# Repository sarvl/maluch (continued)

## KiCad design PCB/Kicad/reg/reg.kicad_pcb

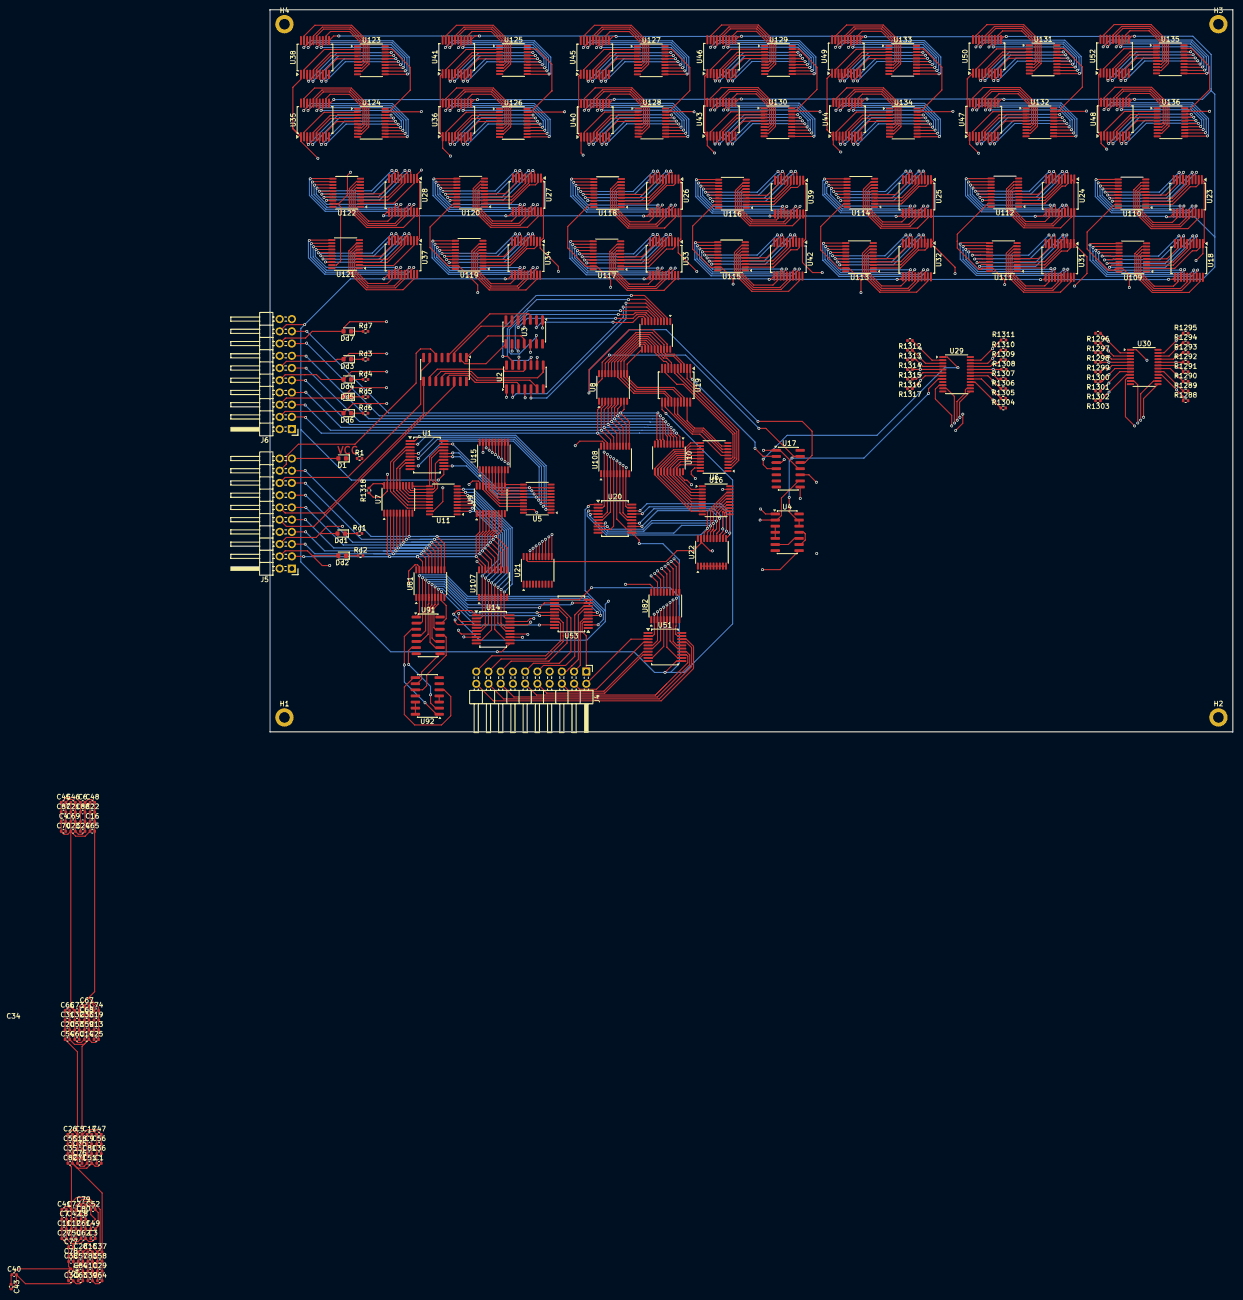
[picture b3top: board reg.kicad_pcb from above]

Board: 6 copper layers, 200.0 x 150.0 mm, 226 parts (0 on the bottom side), 428 nets.

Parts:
C1, C3, C4, C5, C6, C7, C8, C9, C10, C11, C12, C13, C14, C15, C16, C17, C18, C19, C20, C21, C22, C23, C24, C25, C26, C27, C28, C29, C30, C31, C32, C33, C34, C35, C36, C37, C38, C39, C40, C41, C42, C43, C44, C45, C46, C47, C48, C49, C50, C51, C52, C53, C54, C55, C56, C57, C58, C59, C60, C61, C62, C63, C64, C65, C66, C67, C68, C69, C70, C71, C72, C73, C74, C75, C76, C77, C78, C79, C80, C81, C82, C83, C84, C87, C88: 100nF; C_0402_1005Metric
D1: green; D_0603_1608Metric
Dd1, Dd2, Dd3, Dd4, Dd5, Dd6, Dd7: yellow; LED_0603_1608Metric
H1, H2, H3, H4: MountingHole_Pad; MountingHole_2.2mm_M2_DIN965_Pad
J4, J5, J6: Conn_02x10_Odd_Even; PinHeader_2x10_P2.54mm_Horizontal
R1: 680; R_0402_1005Metric
R1288, R1289, R1290, R1291, R1292, R1293, R1294, R1295, R1296, R1297, R1298, R1299, R1300, R1301, R1302, R1303, R1304, R1305, R1306, R1307, R1308, R1309, R1310, R1311, R1312, R1313, R1314, R1315, R1316, R1317, R1318: 10k; R_0402_1005Metric
Rd1, Rd2, Rd3, Rd4, Rd5, Rd6, Rd7: 680; R_0402_1005Metric
U1, U14, U18, U19, U20, U23, U24, U25, U26, U27, U28, U31, U32, U33, U34, U35, U36, U37, U38, U39, U40, U41, U42, U43, U44, U45, U46, U47, U48, U49, U50, U51, U52, U53: 74377; SSOP-20_5.3x7.2mm_P0.65mm
U2, U3, U4: 7400; SO-14_3.9x8.65mm_P1.27mm
U5, U6, U7, U8, U9, U10, U11, U12, U15, U16, U21, U22, U81, U82, U107, U108, U109, U110, U111, U112, U113, U114, U115, U116, U117, U118, U119, U120, U121, U122, U123, U124, U125, U126, U127, U128, U129, U130, U131, U132, U133, U134, U135, U136: 74245; TSSOP-20_4.4x6.5mm_P0.65mm
U17: 7404; SO-14_3.9x8.65mm_P1.27mm
U29, U30: 744067; TSSOP-24_4.4x7.8mm_P0.65mm
U85: 74148; SOIC-16_3.9x9.9mm_P1.27mm
U91, U92: 7408; SO-14_3.9x8.65mm_P1.27mm

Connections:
+5V: C1.1, C3.1, C4.1, C5.1, C6.1, C7.1, C8.1, C9.1, C10.1, C11.1, C12.1, C13.1, C14.1, C15.1, C16.1, C17.1, C18.1, C19.1, C20.1, C21.1, C22.1, C23.1, C24.1, C25.1, C26.1, C27.1, C28.1, C29.1, C30.1, C31.1, C32.1, C33.1, C34.1, C35.1, C36.1, C37.1, C38.1, C39.1, C40.1, C41.1, C42.1, C43.1, C44.1, C45.1, C46.1, C47.1, C48.1, C49.1, C50.1, C51.1, C52.1, C53.1, C54.1, C55.1, C56.1, C57.1, C58.1, C59.1, C60.1, C61.1, C62.1, C63.1, C64.1, C65.1, C66.1, C67.1, C68.1, C69.1, C70.1, C71.1, C72.1, C73.1, C74.1, C75.1, C76.1, C77.1, C78.1, C79.1, C80.1, C81.1, C82.1, C83.1, C84.1, C87.1, C88.1, D1.2 (A), J5.1, J5.19, J6.1, J6.19, R1288.2, R1289.2, R1290.2, R1291.2, R1292.2, R1293.2, R1294.2, R1295.2, R1296.2, R1297.2, R1298.2, R1299.2, R1300.2, R1301.2, R1302.2, R1303.2, R1304.2, R1305.2, R1306.2, R1307.2, R1308.2, R1309.2, R1310.2, R1311.2, R1312.2, R1313.2, R1314.2, R1315.2, R1316.2, R1317.2, R1318.2, U1.20 (VCC), U2.14 (VCC), U3.14 (VCC), U4.14 (VCC), U5.1 (A->B), U5.20 (VCC), U6.1 (A->B), U6.20 (VCC), U7.1 (A->B), U7.20 (VCC), U8.1 (A->B), U8.20 (VCC), U9.1 (A->B), U9.20 (VCC), U10.1 (A->B), U10.20 (VCC), U11.1 (A->B), U11.20 (VCC), U12.1 (A->B), U12.20 (VCC), U14.20 (VCC), U15.1 (A->B), U15.20 (VCC), U16.1 (A->B), U16.20 (VCC), U17.5, U17.14 (VCC), U18.20 (VCC), U19.20 (VCC), U20.20 (VCC), U21.1 (A->B), U21.20 (VCC), U22.1 (A->B), U22.20 (VCC), U23.20 (VCC), U24.20 (VCC), U25.20 (VCC), U26.20 (VCC), U27.20 (VCC), U28.20 (VCC), U29.15 (~E), U29.24 (VCC), U30.15 (~E), U30.24 (VCC), U31.20 (VCC), U32.20 (VCC), U33.20 (VCC), U34.20 (VCC), U35.20 (VCC), U36.20 (VCC), U37.20 (VCC), U38.20 (VCC), U39.20 (VCC), U40.20 (VCC), U41.20 (VCC), U42.20 (VCC), U43.20 (VCC), U44.20 (VCC), U45.20 (VCC), U46.20 (VCC), U47.20 (VCC), U48.20 (VCC), U49.20 (VCC), U50.20 (VCC), U51.20 (VCC), U52.20 (VCC), U53.20 (VCC), U81.1 (A->B), U81.20 (VCC), U82.1 (A->B), U82.20 (VCC), U85.16 (VCC), U91.14 (VCC), U92.12, U92.13, U92.14 (VCC), U107.1 (A->B), U107.20 (VCC), U108.1 (A->B), U108.20 (VCC), U109.1 (A->B), U109.20 (VCC), U110.1 (A->B), U110.20 (VCC), U111.1 (A->B), U111.20 (VCC), U112.1 (A->B), U112.20 (VCC), U113.1 (A->B), U113.20 (VCC), U114.1 (A->B), U114.20 (VCC), U115.1 (A->B), U115.20 (VCC), U116.1 (A->B), U116.20 (VCC), U117.1 (A->B), U117.20 (VCC), U118.1 (A->B), U118.20 (VCC), U119.1 (A->B), U119.20 (VCC), U120.1 (A->B), U120.20 (VCC), U121.1 (A->B), U121.20 (VCC), U122.1 (A->B), U122.20 (VCC), U123.1 (A->B), U123.20 (VCC), U124.1 (A->B), U124.20 (VCC), U125.1 (A->B), U125.20 (VCC), U126.1 (A->B), U126.20 (VCC), U127.1 (A->B), U127.20 (VCC), U128.1 (A->B), U128.20 (VCC), U129.1 (A->B), U129.20 (VCC), U130.1 (A->B), U130.20 (VCC), U131.1 (A->B), U131.20 (VCC), U132.1 (A->B), U132.20 (VCC), U133.1 (A->B), U133.20 (VCC), U134.1 (A->B), U134.20 (VCC), U135.1 (A->B), U135.20 (VCC), U136.1 (A->B), U136.20 (VCC)
/16 bit buffor3/n0E2: U5.19 (CE), U6.19 (CE), U17.8
/16 bit buffor21/OUT0: U5.18 (B0), U9.18 (B0), U15.2 (A0)
/16 bit buffor21/OUT1: U5.17 (B1), U9.17 (B1), U15.3 (A1)
/16 bit buffor21/OUT2: U5.16 (B2), U9.16 (B2), U15.4 (A2)
/16 bit buffor21/OUT3: U5.15 (B3), U9.15 (B3), U15.5 (A3)
/16 bit buffor21/OUT4: U5.14 (B4), U9.14 (B4), U15.6 (A4)
/16 bit buffor21/OUT5: U5.13 (B5), U9.13 (B5), U15.7 (A5)
/16 bit buffor21/OUT6: U5.12 (B6), U9.12 (B6), U15.8 (A6)
/16 bit buffor21/OUT7: U5.11 (B7), U9.11 (B7), U15.9 (A7)
/16 bit buffor21/OUT8: U6.18 (B0), U10.18 (B0), U16.2 (A0)
/16 bit buffor21/OUT9: U6.17 (B1), U10.17 (B1), U16.3 (A1)
/16 bit buffor21/OUT10: U6.16 (B2), U10.16 (B2), U16.4 (A2)
/16 bit buffor21/OUT11: U6.15 (B3), U10.15 (B3), U16.5 (A3)
/16 bit buffor21/OUT12: U6.14 (B4), U10.14 (B4), U16.6 (A4)
/16 bit buffor21/OUT13: U6.13 (B5), U10.13 (B5), U16.7 (A5)
/16 bit buffor21/OUT14: U6.12 (B6), U10.12 (B6), U16.8 (A6)
/16 bit buffor21/OUT15: U6.11 (B7), U10.11 (B7), U16.9 (A7)
/16 bit buffor23/OUT0: U1.3 (D0), U7.18 (B0), U11.18 (B0)
/16 bit buffor23/OUT1: U1.4 (D1), U7.17 (B1), U11.17 (B1)
/16 bit buffor23/OUT2: U1.7 (D2), U7.16 (B2), U11.16 (B2)
/16 bit buffor23/OUT3: U1.8 (D3), U7.15 (B3), U11.15 (B3)
/16 bit buffor23/OUT4: U1.13 (D4), U7.14 (B4), U11.14 (B4)
/16 bit buffor23/OUT5: U1.14 (D5), U7.13 (B5), U11.13 (B5)
/16 bit buffor23/OUT6: U1.17 (D6), U7.12 (B6), U11.12 (B6)
/16 bit buffor23/OUT7: U1.18 (D7), U7.11 (B7), U11.11 (B7)
/16 bit buffor23/OUT8: U8.18 (B0), U12.18 (B0), U19.3 (D0)
/16 bit buffor23/OUT9: U8.17 (B1), U12.17 (B1), U19.4 (D1)
/16 bit buffor23/OUT10: U8.16 (B2), U12.16 (B2), U19.7 (D2)
/16 bit buffor23/OUT11: U8.15 (B3), U12.15 (B3), U19.8 (D3)
/16 bit buffor23/OUT12: U8.14 (B4), U12.14 (B4), U19.13 (D4)
/16 bit buffor23/OUT13: U8.13 (B5), U12.13 (B5), U19.14 (D5)
/16 bit buffor23/OUT14: U8.12 (B6), U12.12 (B6), U19.17 (D6)
/16 bit buffor23/OUT15: U8.11 (B7), U12.11 (B7), U19.18 (D7)
/16 bit buffor23/n0E2: U11.19 (CE), U12.19 (CE), U17.12
/16 bit buffor25/OUT0: U14.3 (D0), U15.18 (B0), U21.18 (B0)
/16 bit buffor25/OUT1: U14.4 (D1), U15.17 (B1), U21.17 (B1)
/16 bit buffor25/OUT2: U14.7 (D2), U15.16 (B2), U21.16 (B2)
/16 bit buffor25/OUT3: U14.8 (D3), U15.15 (B3), U21.15 (B3)
/16 bit buffor25/OUT4: U14.13 (D4), U15.14 (B4), U21.14 (B4)
/16 bit buffor25/OUT5: U14.14 (D5), U15.13 (B5), U21.13 (B5)
/16 bit buffor25/OUT6: U14.17 (D6), U15.12 (B6), U21.12 (B6)
/16 bit buffor25/OUT7: U14.18 (D7), U15.11 (B7), U21.11 (B7)
/16 bit buffor25/OUT8: U16.18 (B0), U20.3 (D0), U22.18 (B0)
/16 bit buffor25/OUT9: U16.17 (B1), U20.4 (D1), U22.17 (B1)
/16 bit buffor25/OUT10: U16.16 (B2), U20.7 (D2), U22.16 (B2)
/16 bit buffor25/OUT11: U16.15 (B3), U20.8 (D3), U22.15 (B3)
/16 bit buffor25/OUT12: U16.14 (B4), U20.13 (D4), U22.14 (B4)
/16 bit buffor25/OUT13: U16.13 (B5), U20.14 (D5), U22.13 (B5)
/16 bit buffor25/OUT14: U16.12 (B6), U20.17 (D6), U22.12 (B6)
/16 bit buffor25/OUT15: U16.11 (B7), U20.18 (D7), U22.11 (B7)
/16 bit buffor26/n0E2: U17.10, U21.19 (CE), U22.19 (CE)
/16 bit buffor28/IN_1_0: U18.2 (Q0), U109.2 (A0)
/16 bit buffor28/IN_1_1: U18.5 (Q1), U109.3 (A1)
/16 bit buffor28/IN_1_2: U18.6 (Q2), U109.4 (A2)
/16 bit buffor28/IN_1_3: U18.9 (Q3), U109.5 (A3)
/16 bit buffor28/IN_1_4: U18.12 (Q4), U109.6 (A4)
/16 bit buffor28/IN_1_5: U18.15 (Q5), U109.7 (A5)
/16 bit buffor28/IN_1_6: U18.16 (Q6), U109.8 (A6)
/16 bit buffor28/IN_1_7: U18.19 (Q7), U109.9 (A7)
/16 bit buffor28/IN_1_8: U23.2 (Q0), U110.2 (A0)
/16 bit buffor28/IN_1_9: U23.5 (Q1), U110.3 (A1)
/16 bit buffor28/IN_1_10: U23.6 (Q2), U110.4 (A2)
/16 bit buffor28/IN_1_11: U23.9 (Q3), U110.5 (A3)
/16 bit buffor28/IN_1_12: U23.12 (Q4), U110.6 (A4)
/16 bit buffor28/IN_1_13: U23.15 (Q5), U110.7 (A5)
/16 bit buffor28/IN_1_14: U23.16 (Q6), U110.8 (A6)
/16 bit buffor28/IN_1_15: U23.19 (Q7), U110.9 (A7)
/16 bit buffor29/IN_1_0: U31.2 (Q0), U111.2 (A0)
/16 bit buffor29/IN_1_1: U31.5 (Q1), U111.3 (A1)
/16 bit buffor29/IN_1_2: U31.6 (Q2), U111.4 (A2)
/16 bit buffor29/IN_1_3: U31.9 (Q3), U111.5 (A3)
/16 bit buffor29/IN_1_4: U31.12 (Q4), U111.6 (A4)
/16 bit buffor29/IN_1_5: U31.15 (Q5), U111.7 (A5)
/16 bit buffor29/IN_1_6: U31.16 (Q6), U111.8 (A6)
/16 bit buffor29/IN_1_7: U31.19 (Q7), U111.9 (A7)
/16 bit buffor29/IN_1_8: U24.2 (Q0), U112.2 (A0)
/16 bit buffor29/IN_1_9: U24.5 (Q1), U112.3 (A1)
/16 bit buffor29/IN_1_10: U24.6 (Q2), U112.4 (A2)
/16 bit buffor29/IN_1_11: U24.9 (Q3), U112.5 (A3)
/16 bit buffor29/IN_1_12: U24.12 (Q4), U112.6 (A4)
/16 bit buffor29/IN_1_13: U24.15 (Q5), U112.7 (A5)
/16 bit buffor29/IN_1_14: U24.16 (Q6), U112.8 (A6)
/16 bit buffor29/IN_1_15: U24.19 (Q7), U112.9 (A7)
/16 bit buffor30/IN_1_0: U32.2 (Q0), U113.2 (A0)
/16 bit buffor30/IN_1_1: U32.5 (Q1), U113.3 (A1)
/16 bit buffor30/IN_1_2: U32.6 (Q2), U113.4 (A2)
/16 bit buffor30/IN_1_3: U32.9 (Q3), U113.5 (A3)
/16 bit buffor30/IN_1_4: U32.12 (Q4), U113.6 (A4)
/16 bit buffor30/IN_1_5: U32.15 (Q5), U113.7 (A5)
/16 bit buffor30/IN_1_6: U32.16 (Q6), U113.8 (A6)
/16 bit buffor30/IN_1_7: U32.19 (Q7), U113.9 (A7)
/16 bit buffor30/IN_1_8: U25.2 (Q0), U114.2 (A0)
/16 bit buffor30/IN_1_9: U25.5 (Q1), U114.3 (A1)
/16 bit buffor30/IN_1_10: U25.6 (Q2), U114.4 (A2)
/16 bit buffor30/IN_1_11: U25.9 (Q3), U114.5 (A3)
/16 bit buffor30/IN_1_12: U25.12 (Q4), U114.6 (A4)
/16 bit buffor30/IN_1_13: U25.15 (Q5), U114.7 (A5)
/16 bit buffor30/IN_1_14: U25.16 (Q6), U114.8 (A6)
/16 bit buffor30/IN_1_15: U25.19 (Q7), U114.9 (A7)
/16 bit buffor31/IN_1_0: U42.2 (Q0), U115.2 (A0)
/16 bit buffor31/IN_1_1: U42.5 (Q1), U115.3 (A1)
/16 bit buffor31/IN_1_2: U42.6 (Q2), U115.4 (A2)
/16 bit buffor31/IN_1_3: U42.9 (Q3), U115.5 (A3)
/16 bit buffor31/IN_1_4: U42.12 (Q4), U115.6 (A4)
/16 bit buffor31/IN_1_5: U42.15 (Q5), U115.7 (A5)
/16 bit buffor31/IN_1_6: U42.16 (Q6), U115.8 (A6)
/16 bit buffor31/IN_1_7: U42.19 (Q7), U115.9 (A7)
/16 bit buffor31/IN_1_8: U39.2 (Q0), U116.2 (A0)
/16 bit buffor31/IN_1_9: U39.5 (Q1), U116.3 (A1)
/16 bit buffor31/IN_1_10: U39.6 (Q2), U116.4 (A2)
/16 bit buffor31/IN_1_11: U39.9 (Q3), U116.5 (A3)
/16 bit buffor31/IN_1_12: U39.12 (Q4), U116.6 (A4)
/16 bit buffor31/IN_1_13: U39.15 (Q5), U116.7 (A5)
/16 bit buffor31/IN_1_14: U39.16 (Q6), U116.8 (A6)
/16 bit buffor31/IN_1_15: U39.19 (Q7), U116.9 (A7)
/16 bit buffor32/IN_1_0: U33.2 (Q0), U117.2 (A0)
/16 bit buffor32/IN_1_1: U33.5 (Q1), U117.3 (A1)
/16 bit buffor32/IN_1_2: U33.6 (Q2), U117.4 (A2)
/16 bit buffor32/IN_1_3: U33.9 (Q3), U117.5 (A3)
/16 bit buffor32/IN_1_4: U33.12 (Q4), U117.6 (A4)
/16 bit buffor32/IN_1_5: U33.15 (Q5), U117.7 (A5)
/16 bit buffor32/IN_1_6: U33.16 (Q6), U117.8 (A6)
/16 bit buffor32/IN_1_7: U33.19 (Q7), U117.9 (A7)
/16 bit buffor32/IN_1_8: U26.2 (Q0), U118.2 (A0)
/16 bit buffor32/IN_1_9: U26.5 (Q1), U118.3 (A1)
/16 bit buffor32/IN_1_10: U26.6 (Q2), U118.4 (A2)
/16 bit buffor32/IN_1_11: U26.9 (Q3), U118.5 (A3)
/16 bit buffor32/IN_1_12: U26.12 (Q4), U118.6 (A4)
/16 bit buffor32/IN_1_13: U26.15 (Q5), U118.7 (A5)
/16 bit buffor32/IN_1_14: U26.16 (Q6), U118.8 (A6)
/16 bit buffor32/IN_1_15: U26.19 (Q7), U118.9 (A7)
/16 bit buffor33/IN_1_0: U34.2 (Q0), U119.2 (A0)
/16 bit buffor33/IN_1_1: U34.5 (Q1), U119.3 (A1)
/16 bit buffor33/IN_1_2: U34.6 (Q2), U119.4 (A2)
/16 bit buffor33/IN_1_3: U34.9 (Q3), U119.5 (A3)
/16 bit buffor33/IN_1_4: U34.12 (Q4), U119.6 (A4)
/16 bit buffor33/IN_1_5: U34.15 (Q5), U119.7 (A5)
/16 bit buffor33/IN_1_6: U34.16 (Q6), U119.8 (A6)
/16 bit buffor33/IN_1_7: U34.19 (Q7), U119.9 (A7)
/16 bit buffor33/IN_1_8: U27.2 (Q0), U120.2 (A0)
/16 bit buffor33/IN_1_9: U27.5 (Q1), U120.3 (A1)
/16 bit buffor33/IN_1_10: U27.6 (Q2), U120.4 (A2)
/16 bit buffor33/IN_1_11: U27.9 (Q3), U120.5 (A3)
/16 bit buffor33/IN_1_12: U27.12 (Q4), U120.6 (A4)
/16 bit buffor33/IN_1_13: U27.15 (Q5), U120.7 (A5)
/16 bit buffor33/IN_1_14: U27.16 (Q6), U120.8 (A6)
/16 bit buffor33/IN_1_15: U27.19 (Q7), U120.9 (A7)
/16 bit buffor34/IN_1_0: U37.2 (Q0), U121.2 (A0)
/16 bit buffor34/IN_1_1: U37.5 (Q1), U121.3 (A1)
/16 bit buffor34/IN_1_2: U37.6 (Q2), U121.4 (A2)
/16 bit buffor34/IN_1_3: U37.9 (Q3), U121.5 (A3)
/16 bit buffor34/IN_1_4: U37.12 (Q4), U121.6 (A4)
/16 bit buffor34/IN_1_5: U37.15 (Q5), U121.7 (A5)
/16 bit buffor34/IN_1_6: U37.16 (Q6), U121.8 (A6)
/16 bit buffor34/IN_1_7: U37.19 (Q7), U121.9 (A7)
/16 bit buffor34/IN_1_8: U28.2 (Q0), U122.2 (A0)
/16 bit buffor34/IN_1_9: U28.5 (Q1), U122.3 (A1)
/16 bit buffor34/IN_1_10: U28.6 (Q2), U122.4 (A2)
/16 bit buffor34/IN_1_11: U28.9 (Q3), U122.5 (A3)
/16 bit buffor34/IN_1_12: U28.12 (Q4), U122.6 (A4)
/16 bit buffor34/IN_1_13: U28.15 (Q5), U122.7 (A5)
/16 bit buffor34/IN_1_14: U28.16 (Q6), U122.8 (A6)
/16 bit buffor34/IN_1_15: U28.19 (Q7), U122.9 (A7)
/16 bit buffor35/IN_1_0: U38.2 (Q0), U123.2 (A0)
/16 bit buffor35/IN_1_1: U38.5 (Q1), U123.3 (A1)
/16 bit buffor35/IN_1_2: U38.6 (Q2), U123.4 (A2)
/16 bit buffor35/IN_1_3: U38.9 (Q3), U123.5 (A3)
/16 bit buffor35/IN_1_4: U38.12 (Q4), U123.6 (A4)
/16 bit buffor35/IN_1_5: U38.15 (Q5), U123.7 (A5)
/16 bit buffor35/IN_1_6: U38.16 (Q6), U123.8 (A6)
/16 bit buffor35/IN_1_7: U38.19 (Q7), U123.9 (A7)
/16 bit buffor35/IN_1_8: U35.2 (Q0), U124.2 (A0)
/16 bit buffor35/IN_1_9: U35.5 (Q1), U124.3 (A1)
/16 bit buffor35/IN_1_10: U35.6 (Q2), U124.4 (A2)
/16 bit buffor35/IN_1_11: U35.9 (Q3), U124.5 (A3)
/16 bit buffor35/IN_1_12: U35.12 (Q4), U124.6 (A4)
/16 bit buffor35/IN_1_13: U35.15 (Q5), U124.7 (A5)
/16 bit buffor35/IN_1_14: U35.16 (Q6), U124.8 (A6)
/16 bit buffor35/IN_1_15: U35.19 (Q7), U124.9 (A7)
/16 bit buffor36/IN_1_0: U41.2 (Q0), U125.2 (A0)
/16 bit buffor36/IN_1_1: U41.5 (Q1), U125.3 (A1)
/16 bit buffor36/IN_1_2: U41.6 (Q2), U125.4 (A2)
/16 bit buffor36/IN_1_3: U41.9 (Q3), U125.5 (A3)
/16 bit buffor36/IN_1_4: U41.12 (Q4), U125.6 (A4)
/16 bit buffor36/IN_1_5: U41.15 (Q5), U125.7 (A5)
/16 bit buffor36/IN_1_6: U41.16 (Q6), U125.8 (A6)
/16 bit buffor36/IN_1_7: U41.19 (Q7), U125.9 (A7)
/16 bit buffor36/IN_1_8: U36.2 (Q0), U126.2 (A0)
/16 bit buffor36/IN_1_9: U36.5 (Q1), U126.3 (A1)
/16 bit buffor36/IN_1_10: U36.6 (Q2), U126.4 (A2)
/16 bit buffor36/IN_1_11: U36.9 (Q3), U126.5 (A3)
/16 bit buffor36/IN_1_12: U36.12 (Q4), U126.6 (A4)
/16 bit buffor36/IN_1_13: U36.15 (Q5), U126.7 (A5)
/16 bit buffor36/IN_1_14: U36.16 (Q6), U126.8 (A6)
/16 bit buffor36/IN_1_15: U36.19 (Q7), U126.9 (A7)
/16 bit buffor37/IN_1_0: U45.2 (Q0), U127.2 (A0)
/16 bit buffor37/IN_1_1: U45.5 (Q1), U127.3 (A1)
/16 bit buffor37/IN_1_2: U45.6 (Q2), U127.4 (A2)
/16 bit buffor37/IN_1_3: U45.9 (Q3), U127.5 (A3)
/16 bit buffor37/IN_1_4: U45.12 (Q4), U127.6 (A4)
/16 bit buffor37/IN_1_5: U45.15 (Q5), U127.7 (A5)
/16 bit buffor37/IN_1_6: U45.16 (Q6), U127.8 (A6)
/16 bit buffor37/IN_1_7: U45.19 (Q7), U127.9 (A7)
/16 bit buffor37/IN_1_8: U40.2 (Q0), U128.2 (A0)
/16 bit buffor37/IN_1_9: U40.5 (Q1), U128.3 (A1)
/16 bit buffor37/IN_1_10: U40.6 (Q2), U128.4 (A2)
/16 bit buffor37/IN_1_11: U40.9 (Q3), U128.5 (A3)
/16 bit buffor37/IN_1_12: U40.12 (Q4), U128.6 (A4)
/16 bit buffor37/IN_1_13: U40.15 (Q5), U128.7 (A5)
/16 bit buffor37/IN_1_14: U40.16 (Q6), U128.8 (A6)
/16 bit buffor37/IN_1_15: U40.19 (Q7), U128.9 (A7)
/16 bit buffor38/IN_1_0: U46.2 (Q0), U129.2 (A0)
/16 bit buffor38/IN_1_1: U46.5 (Q1), U129.3 (A1)
/16 bit buffor38/IN_1_2: U46.6 (Q2), U129.4 (A2)
/16 bit buffor38/IN_1_3: U46.9 (Q3), U129.5 (A3)
/16 bit buffor38/IN_1_4: U46.12 (Q4), U129.6 (A4)
/16 bit buffor38/IN_1_5: U46.15 (Q5), U129.7 (A5)
/16 bit buffor38/IN_1_6: U46.16 (Q6), U129.8 (A6)
/16 bit buffor38/IN_1_7: U46.19 (Q7), U129.9 (A7)
/16 bit buffor38/IN_1_8: U43.2 (Q0), U130.2 (A0)
/16 bit buffor38/IN_1_9: U43.5 (Q1), U130.3 (A1)
/16 bit buffor38/IN_1_10: U43.6 (Q2), U130.4 (A2)
/16 bit buffor38/IN_1_11: U43.9 (Q3), U130.5 (A3)
/16 bit buffor38/IN_1_12: U43.12 (Q4), U130.6 (A4)
/16 bit buffor38/IN_1_13: U43.15 (Q5), U130.7 (A5)
/16 bit buffor38/IN_1_14: U43.16 (Q6), U130.8 (A6)
/16 bit buffor38/IN_1_15: U43.19 (Q7), U130.9 (A7)
/16 bit buffor39/IN_1_0: U50.2 (Q0), U131.2 (A0)
/16 bit buffor39/IN_1_1: U50.5 (Q1), U131.3 (A1)
/16 bit buffor39/IN_1_2: U50.6 (Q2), U131.4 (A2)
/16 bit buffor39/IN_1_3: U50.9 (Q3), U131.5 (A3)
/16 bit buffor39/IN_1_4: U50.12 (Q4), U131.6 (A4)
/16 bit buffor39/IN_1_5: U50.15 (Q5), U131.7 (A5)
/16 bit buffor39/IN_1_6: U50.16 (Q6), U131.8 (A6)
/16 bit buffor39/IN_1_7: U50.19 (Q7), U131.9 (A7)
/16 bit buffor39/IN_1_8: U47.2 (Q0), U132.2 (A0)
/16 bit buffor39/IN_1_9: U47.5 (Q1), U132.3 (A1)
/16 bit buffor39/IN_1_10: U47.6 (Q2), U132.4 (A2)
/16 bit buffor39/IN_1_11: U47.9 (Q3), U132.5 (A3)
/16 bit buffor39/IN_1_12: U47.12 (Q4), U132.6 (A4)
/16 bit buffor39/IN_1_13: U47.15 (Q5), U132.7 (A5)
/16 bit buffor39/IN_1_14: U47.16 (Q6), U132.8 (A6)
/16 bit buffor39/IN_1_15: U47.19 (Q7), U132.9 (A7)
/16 bit buffor40/IN_1_0: U49.2 (Q0), U133.2 (A0)
/16 bit buffor40/IN_1_1: U49.5 (Q1), U133.3 (A1)
/16 bit buffor40/IN_1_2: U49.6 (Q2), U133.4 (A2)
/16 bit buffor40/IN_1_3: U49.9 (Q3), U133.5 (A3)
/16 bit buffor40/IN_1_4: U49.12 (Q4), U133.6 (A4)
/16 bit buffor40/IN_1_5: U49.15 (Q5), U133.7 (A5)
/16 bit buffor40/IN_1_6: U49.16 (Q6), U133.8 (A6)
/16 bit buffor40/IN_1_7: U49.19 (Q7), U133.9 (A7)
/16 bit buffor40/IN_1_8: U44.2 (Q0), U134.2 (A0)
/16 bit buffor40/IN_1_9: U44.5 (Q1), U134.3 (A1)
/16 bit buffor40/IN_1_10: U44.6 (Q2), U134.4 (A2)
/16 bit buffor40/IN_1_11: U44.9 (Q3), U134.5 (A3)
/16 bit buffor40/IN_1_12: U44.12 (Q4), U134.6 (A4)
/16 bit buffor40/IN_1_13: U44.15 (Q5), U134.7 (A5)
/16 bit buffor40/IN_1_14: U44.16 (Q6), U134.8 (A6)
/16 bit buffor40/IN_1_15: U44.19 (Q7), U134.9 (A7)
/16 bit buffor41/IN_1_0: U52.2 (Q0), U135.2 (A0)
/16 bit buffor41/IN_1_1: U52.5 (Q1), U135.3 (A1)
/16 bit buffor41/IN_1_2: U52.6 (Q2), U135.4 (A2)
/16 bit buffor41/IN_1_3: U52.9 (Q3), U135.5 (A3)
/16 bit buffor41/IN_1_4: U52.12 (Q4), U135.6 (A4)
/16 bit buffor41/IN_1_5: U52.15 (Q5), U135.7 (A5)
/16 bit buffor41/IN_1_6: U52.16 (Q6), U135.8 (A6)
/16 bit buffor41/IN_1_7: U52.19 (Q7), U135.9 (A7)
/16 bit buffor41/IN_1_8: U48.2 (Q0), U136.2 (A0)
/16 bit buffor41/IN_1_9: U48.5 (Q1), U136.3 (A1)
/16 bit buffor41/IN_1_10: U48.6 (Q2), U136.4 (A2)
/16 bit buffor41/IN_1_11: U48.9 (Q3), U136.5 (A3)
/16 bit buffor41/IN_1_12: U48.12 (Q4), U136.6 (A4)
/16 bit buffor41/IN_1_13: U48.15 (Q5), U136.7 (A5)
/16 bit buffor41/IN_1_14: U48.16 (Q6), U136.8 (A6)
/16 bit buffor41/IN_1_15: U48.19 (Q7), U136.9 (A7)
/16 bit register17/nWE: U4.8, U14.1 (~E), U20.1 (~E)
/16 bit register18/nWE: U1.1 (~E), U17.2, U19.1 (~E)
/ID_REG_SEL_0: Dd6.2 (A), J6.4, U29.10 (S0), U30.10 (S0)
/ID_REG_SEL_1: Dd5.2 (A), J6.6, U29.11 (S1), U30.11 (S1)
/ID_REG_SEL_2: Dd4.2 (A), J6.10, U29.14 (S2), U30.14 (S2)
/ID_REG_SEL_3: Dd3.2 (A), J6.12, U29.13 (S3), U30.13 (S3)
/INT: J5.10, U85.14 (~GS)
/IO0: J4.1, U53.3 (D0)
/IO1: J4.3, U53.4 (D1)
/IO2: J4.5, U53.7 (D2)
/IO3: J4.9, U53.8 (D3)
/IO4: J4.11, U53.13 (D4)
/IO5: J4.15, U53.14 (D5)
/IO6: J4.17, U53.17 (D6)
/IO7: J4.19, U53.18 (D7)
/IO8: J4.2, U51.3 (D0)
/IO9: J4.4, U51.4 (D1)
/IO10: J4.6, U51.7 (D2)
/IO11: J4.10, U51.8 (D3)
/IO12: J4.12, U51.13 (D4)
/IO13: J4.16, U51.14 (D5)
/IO14: J4.18, U51.17 (D6)
/IO15: J4.20, U51.18 (D7)
/Interupt_ID_0: J5.12, U85.9 (~S0)
/Interupt_ID_1: J5.16, U85.7 (~S1)
/Interupt_ID_2: J5.18, U85.6 (~S2)
/OUT_1_2: R1317.1, U18.1 (~E), U23.1 (~E), U29.7 (I2)
/OUT_1_3: R1316.1, U24.1 (~E), U29.6 (I3), U31.1 (~E)
/OUT_1_4: R1315.1, U25.1 (~E), U29.5 (I4), U32.1 (~E)
/OUT_1_5: R1314.1, U29.4 (I5), U39.1 (~E), U42.1 (~E)
/OUT_1_6: R1313.1, U26.1 (~E), U29.3 (I6), U33.1 (~E)
/OUT_1_7: R1312.1, U27.1 (~E), U29.2 (I7), U34.1 (~E)
/OUT_1_8: R1311.1, U28.1 (~E), U29.23 (I8), U37.1 (~E)
/OUT_1_9: R1310.1, U29.22 (I9), U35.1 (~E), U38.1 (~E)
/OUT_1_10: R1309.1, U29.21 (I10), U36.1 (~E), U41.1 (~E)
/OUT_1_11: R1308.1, U29.20 (I11), U40.1 (~E), U45.1 (~E)
/OUT_1_12: R1307.1, U29.19 (I12), U43.1 (~E), U46.1 (~E)
/OUT_1_13: R1306.1, U29.18 (I13), U44.1 (~E), U49.1 (~E)
/OUT_1_14: R1305.1, U29.17 (I14), U47.1 (~E), U50.1 (~E)
/OUT_1_15: R1304.1, U29.16 (I15), U48.1 (~E), U52.1 (~E)
/OUT_5_0: U53.2 (Q0), U81.2 (A0), U91.1
/OUT_5_1: U53.5 (Q1), U81.3 (A1), U91.2
/OUT_5_2: U53.6 (Q2), U81.4 (A2), U91.4
/OUT_5_3: U53.9 (Q3), U81.5 (A3), U91.5
/OUT_5_4: U53.12 (Q4), U81.6 (A4), U91.9
/OUT_5_5: U53.15 (Q5), U81.7 (A5), U91.10
/OUT_5_6: U53.16 (Q6), U81.8 (A6), U91.12
/OUT_5_7: U53.19 (Q7), U81.9 (A7), U91.13
/OUT_5_8: U2.12, U51.2 (Q0), U82.2 (A0)
/OUT_5_9: U2.9, U51.5 (Q1), U82.3 (A1)
/OUT_5_10: U2.4, U51.6 (Q2), U82.4 (A2)
/OUT_5_11: U2.1, U51.9 (Q3), U82.5 (A3)
/OUT_5_12: U3.12, U51.12 (Q4), U82.6 (A4)
/OUT_5_13: U3.9, U51.15 (Q5), U82.7 (A5)
/OUT_5_14: U3.4, U51.16 (Q6), U82.8 (A6)
/OUT_5_15: U3.1, U51.19 (Q7), U82.9 (A7)
/OUT_7_0: R1303.1, U30.9 (I0), U81.19 (CE), U82.19 (CE)
/OUT_7_1: R1302.1, U30.8 (I1), U107.19 (CE), U108.19 (CE)
/OUT_7_2: R1301.1, U30.7 (I2), U109.19 (CE), U110.19 (CE)
/OUT_7_3: R1300.1, U30.6 (I3), U111.19 (CE), U112.19 (CE)
/OUT_7_4: R1299.1, U30.5 (I4), U113.19 (CE), U114.19 (CE)
/OUT_7_5: R1298.1, U30.4 (I5), U115.19 (CE), U116.19 (CE)
/OUT_7_6: R1297.1, U30.3 (I6), U117.19 (CE), U118.19 (CE)
/OUT_7_7: R1296.1, U30.2 (I7), U119.19 (CE), U120.19 (CE)
/OUT_7_8: R1295.1, U30.23 (I8), U121.19 (CE), U122.19 (CE)
/OUT_7_9: R1294.1, U30.22 (I9), U123.19 (CE), U124.19 (CE)
/OUT_7_10: R1293.1, U30.21 (I10), U125.19 (CE), U126.19 (CE)
/OUT_7_11: R1292.1, U30.20 (I11), U127.19 (CE), U128.19 (CE)
/OUT_7_12: R1291.1, U30.19 (I12), U129.19 (CE), U130.19 (CE)
/OUT_7_13: R1290.1, U30.18 (I13), U133.19 (CE), U134.19 (CE)
/OUT_7_14: R1289.1, U30.17 (I14), U131.19 (CE), U132.19 (CE)
/OUT_7_15: R1288.1, U30.16 (I15), U135.19 (CE), U136.19 (CE)
/clk: J6.18, U1.11 (CP), U14.11 (CP), U18.11 (CP), U19.11 (CP), U20.11 (CP), U23.11 (CP), U24.11 (CP), U25.11 (CP), U26.11 (CP), U27.11 (CP), U28.11 (CP), U31.11 (CP), U32.11 (CP), U33.11 (CP), U34.11 (CP), U35.11 (CP), U36.11 (CP), U37.11 (CP), U38.11 (CP), U39.11 (CP), U40.11 (CP), U41.11 (CP), U42.11 (CP), U43.11 (CP), U44.11 (CP), U45.11 (CP), U46.11 (CP), U47.11 (CP), U48.11 (CP), U49.11 (CP), U50.11 (CP), U51.11 (CP), U52.11 (CP), U53.11 (CP)
/data0: J5.3, U7.2 (A0), U9.2 (A0), U18.3 (D0), U31.3 (D0), U32.3 (D0), U33.3 (D0), U34.3 (D0), U37.3 (D0), U38.3 (D0), U41.3 (D0), U42.3 (D0), U45.3 (D0), U46.3 (D0), U49.3 (D0), U50.3 (D0), U52.3 (D0), U81.18 (B0), U107.18 (B0), U109.18 (B0), U111.18 (B0), U113.18 (B0), U115.18 (B0), U117.18 (B0), U119.18 (B0), U121.18 (B0), U123.18 (B0), U125.18 (B0), U127.18 (B0), U129.18 (B0), U131.18 (B0), U133.18 (B0), U135.18 (B0)
/data1: J5.5, U7.3 (A1), U9.3 (A1), U18.4 (D1), U31.4 (D1), U32.4 (D1), U33.4 (D1), U34.4 (D1), U37.4 (D1), U38.4 (D1), U41.4 (D1), U42.4 (D1), U45.4 (D1), U46.4 (D1), U49.4 (D1), U50.4 (D1), U52.4 (D1), U81.17 (B1), U107.17 (B1), U109.17 (B1), U111.17 (B1), U113.17 (B1), U115.17 (B1), U117.17 (B1), U119.17 (B1), U121.17 (B1), U123.17 (B1), U125.17 (B1), U127.17 (B1), U129.17 (B1), U131.17 (B1), U133.17 (B1), U135.17 (B1)
/data2: J5.7, U7.4 (A2), U9.4 (A2), U18.7 (D2), U31.7 (D2), U32.7 (D2), U33.7 (D2), U34.7 (D2), U37.7 (D2), U38.7 (D2), U41.7 (D2), U42.7 (D2), U45.7 (D2), U46.7 (D2), U49.7 (D2), U50.7 (D2), U52.7 (D2), U81.16 (B2), U107.16 (B2), U109.16 (B2), U111.16 (B2), U113.16 (B2), U115.16 (B2), U117.16 (B2), U119.16 (B2), U121.16 (B2), U123.16 (B2), U125.16 (B2), U127.16 (B2), U129.16 (B2), U131.16 (B2), U133.16 (B2), U135.16 (B2)
/data3: J5.9, U7.5 (A3), U9.5 (A3), U18.8 (D3), U31.8 (D3), U32.8 (D3), U33.8 (D3), U34.8 (D3), U37.8 (D3), U38.8 (D3), U41.8 (D3), U42.8 (D3), U45.8 (D3), U46.8 (D3), U49.8 (D3), U50.8 (D3), U52.8 (D3), U81.15 (B3), U107.15 (B3), U109.15 (B3), U111.15 (B3), U113.15 (B3), U115.15 (B3), U117.15 (B3), U119.15 (B3), U121.15 (B3), U123.15 (B3), U125.15 (B3), U127.15 (B3), U129.15 (B3), U131.15 (B3), U133.15 (B3), U135.15 (B3)
/data4: J5.11, U7.6 (A4), U9.6 (A4), U18.13 (D4), U31.13 (D4), U32.13 (D4), U33.13 (D4), U34.13 (D4), U37.13 (D4), U38.13 (D4), U41.13 (D4), U42.13 (D4), U45.13 (D4), U46.13 (D4), U49.13 (D4), U50.13 (D4), U52.13 (D4), U81.14 (B4), U107.14 (B4), U109.14 (B4), U111.14 (B4), U113.14 (B4), U115.14 (B4), U117.14 (B4), U119.14 (B4), U121.14 (B4), U123.14 (B4), U125.14 (B4), U127.14 (B4), U129.14 (B4), U131.14 (B4), U133.14 (B4), U135.14 (B4)
/data5: J5.13, U7.7 (A5), U9.7 (A5), U18.14 (D5), U31.14 (D5), U32.14 (D5), U33.14 (D5), U34.14 (D5), U37.14 (D5), U38.14 (D5), U41.14 (D5), U42.14 (D5), U45.14 (D5), U46.14 (D5), U49.14 (D5), U50.14 (D5), U52.14 (D5), U81.13 (B5), U107.13 (B5), U109.13 (B5), U111.13 (B5), U113.13 (B5), U115.13 (B5), U117.13 (B5), U119.13 (B5), U121.13 (B5), U123.13 (B5), U125.13 (B5), U127.13 (B5), U129.13 (B5), U131.13 (B5), U133.13 (B5), U135.13 (B5)
/data6: J5.15, U7.8 (A6), U9.8 (A6), U18.17 (D6), U31.17 (D6), U32.17 (D6), U33.17 (D6), U34.17 (D6), U37.17 (D6), U38.17 (D6), U41.17 (D6), U42.17 (D6), U45.17 (D6), U46.17 (D6), U49.17 (D6), U50.17 (D6), U52.17 (D6), U81.12 (B6), U107.12 (B6), U109.12 (B6), U111.12 (B6), U113.12 (B6), U115.12 (B6), U117.12 (B6), U119.12 (B6), U121.12 (B6), U123.12 (B6), U125.12 (B6), U127.12 (B6), U129.12 (B6), U131.12 (B6), U133.12 (B6), U135.12 (B6)
/data7: J5.17, U7.9 (A7), U9.9 (A7), U18.18 (D7), U31.18 (D7), U32.18 (D7), U33.18 (D7), U34.18 (D7), U37.18 (D7), U38.18 (D7), U41.18 (D7), U42.18 (D7), U45.18 (D7), U46.18 (D7), U49.18 (D7), U50.18 (D7), U52.18 (D7), U81.11 (B7), U107.11 (B7), U109.11 (B7), U111.11 (B7), U113.11 (B7), U115.11 (B7), U117.11 (B7), U119.11 (B7), U121.11 (B7), U123.11 (B7), U125.11 (B7), U127.11 (B7), U129.11 (B7), U131.11 (B7), U133.11 (B7), U135.11 (B7)
/data8: J6.3, U8.2 (A0), U10.2 (A0), U23.3 (D0), U24.3 (D0), U25.3 (D0), U26.3 (D0), U27.3 (D0), U28.3 (D0), U35.3 (D0), U36.3 (D0), U39.3 (D0), U40.3 (D0), U43.3 (D0), U44.3 (D0), U47.3 (D0), U48.3 (D0), U82.18 (B0), U108.18 (B0), U110.18 (B0), U112.18 (B0), U114.18 (B0), U116.18 (B0), U118.18 (B0), U120.18 (B0), U122.18 (B0), U124.18 (B0), U126.18 (B0), U128.18 (B0), U130.18 (B0), U132.18 (B0), U134.18 (B0), U136.18 (B0)
/data9: J6.5, U8.3 (A1), U10.3 (A1), U23.4 (D1), U24.4 (D1), U25.4 (D1), U26.4 (D1), U27.4 (D1), U28.4 (D1), U35.4 (D1), U36.4 (D1), U39.4 (D1), U40.4 (D1), U43.4 (D1), U44.4 (D1), U47.4 (D1), U48.4 (D1), U82.17 (B1), U108.17 (B1), U110.17 (B1), U112.17 (B1), U114.17 (B1), U116.17 (B1), U118.17 (B1), U120.17 (B1), U122.17 (B1), U124.17 (B1), U126.17 (B1), U128.17 (B1), U130.17 (B1), U132.17 (B1), U134.17 (B1), U136.17 (B1)
/data10: J6.7, U8.4 (A2), U10.4 (A2), U23.7 (D2), U24.7 (D2), U25.7 (D2), U26.7 (D2), U27.7 (D2), U28.7 (D2), U35.7 (D2), U36.7 (D2), U39.7 (D2), U40.7 (D2), U43.7 (D2), U44.7 (D2), U47.7 (D2), U48.7 (D2), U82.16 (B2), U108.16 (B2), U110.16 (B2), U112.16 (B2), U114.16 (B2), U116.16 (B2), U118.16 (B2), U120.16 (B2), U122.16 (B2), U124.16 (B2), U126.16 (B2), U128.16 (B2), U130.16 (B2), U132.16 (B2), U134.16 (B2), U136.16 (B2)
/data11: J6.9, U8.5 (A3), U10.5 (A3), U23.8 (D3), U24.8 (D3), U25.8 (D3), U26.8 (D3), U27.8 (D3), U28.8 (D3), U35.8 (D3), U36.8 (D3), U39.8 (D3), U40.8 (D3), U43.8 (D3), U44.8 (D3), U47.8 (D3), U48.8 (D3), U82.15 (B3), U108.15 (B3), U110.15 (B3), U112.15 (B3), U114.15 (B3), U116.15 (B3), U118.15 (B3), U120.15 (B3), U122.15 (B3), U124.15 (B3), U126.15 (B3), U128.15 (B3), U130.15 (B3), U132.15 (B3), U134.15 (B3), U136.15 (B3)
/data12: J6.11, U8.6 (A4), U10.6 (A4), U23.13 (D4), U24.13 (D4), U25.13 (D4), U26.13 (D4), U27.13 (D4), U28.13 (D4), U35.13 (D4), U36.13 (D4), U39.13 (D4), U40.13 (D4), U43.13 (D4), U44.13 (D4), U47.13 (D4), U48.13 (D4), U82.14 (B4), U108.14 (B4), U110.14 (B4), U112.14 (B4), U114.14 (B4), U116.14 (B4), U118.14 (B4), U120.14 (B4), U122.14 (B4), U124.14 (B4), U126.14 (B4), U128.14 (B4), U130.14 (B4), U132.14 (B4), U134.14 (B4), U136.14 (B4)
/data13: J6.13, U8.7 (A5), U10.7 (A5), U23.14 (D5), U24.14 (D5), U25.14 (D5), U26.14 (D5), U27.14 (D5), U28.14 (D5), U35.14 (D5), U36.14 (D5), U39.14 (D5), U40.14 (D5), U43.14 (D5), U44.14 (D5), U47.14 (D5), U48.14 (D5), U82.13 (B5), U108.13 (B5), U110.13 (B5), U112.13 (B5), U114.13 (B5), U116.13 (B5), U118.13 (B5), U120.13 (B5), U122.13 (B5), U124.13 (B5), U126.13 (B5), U128.13 (B5), U130.13 (B5), U132.13 (B5), U134.13 (B5), U136.13 (B5)
/data14: J6.15, U8.8 (A6), U10.8 (A6), U23.17 (D6), U24.17 (D6), U25.17 (D6), U26.17 (D6), U27.17 (D6), U28.17 (D6), U35.17 (D6), U36.17 (D6), U39.17 (D6), U40.17 (D6), U43.17 (D6), U44.17 (D6), U47.17 (D6), U48.17 (D6), U82.12 (B6), U108.12 (B6), U110.12 (B6), U112.12 (B6), U114.12 (B6), U116.12 (B6), U118.12 (B6), U120.12 (B6), U122.12 (B6), U124.12 (B6), U126.12 (B6), U128.12 (B6), U130.12 (B6), U132.12 (B6), U134.12 (B6), U136.12 (B6)
/data15: J6.17, U8.9 (A7), U10.9 (A7), U23.18 (D7), U24.18 (D7), U25.18 (D7), U26.18 (D7), U27.18 (D7), U28.18 (D7), U35.18 (D7), U36.18 (D7), U39.18 (D7), U40.18 (D7), U43.18 (D7), U44.18 (D7), U47.18 (D7), U48.18 (D7), U82.11 (B7), U108.11 (B7), U110.11 (B7), U112.11 (B7), U114.11 (B7), U116.11 (B7), U118.11 (B7), U120.11 (B7), U122.11 (B7), U124.11 (B7), U126.11 (B7), U128.11 (B7), U130.11 (B7), U132.11 (B7), U134.11 (B7), U136.11 (B7)
/mask_restore: Dd2.2 (A), J5.4, U4.2, U9.19 (CE), U10.19 (CE), U17.9
/mask_save: Dd1.2 (A), J5.6, U4.1, U15.19 (CE), U16.19 (CE), U17.1, U17.11
/mask_saved0: U1.2 (Q0), U5.2 (A0)
/mask_saved1: U1.5 (Q1), U5.3 (A1)
/mask_saved2: U1.6 (Q2), U5.4 (A2)
/mask_saved3: U1.9 (Q3), U5.5 (A3)
/mask_saved4: U1.12 (Q4), U5.6 (A4)
/mask_saved5: U1.15 (Q5), U5.7 (A5)
/mask_saved6: U1.16 (Q6), U5.8 (A6)
/mask_saved7: U1.19 (Q7), U5.9 (A7)
/mask_saved8: U6.2 (A0), U19.2 (Q0)
/mask_saved9: U6.3 (A1), U19.5 (Q1)
/mask_saved10: U6.4 (A2), U19.6 (Q2)
/mask_saved11: U6.5 (A3), U19.9 (Q3)
/mask_saved12: U6.6 (A4), U19.12 (Q4)
/mask_saved13: U6.7 (A5), U19.15 (Q5)
/mask_saved14: U6.8 (A6), U19.16 (Q6)
/mask_saved15: U6.9 (A7), U19.19 (Q7)
/octal_nand/out_0: U2.11, U85.10 (~IO)
/octal_nand/out_1: U2.8, U85.11 (~I1)
/octal_nand/out_2: U2.6, U85.12 (~I2)
/octal_nand/out_3: U2.3, U85.13 (~I3)
/octal_nand/out_4: U3.11, U85.1 (~I4)
/octal_nand/out_5: U3.8, U85.2 (~I5)
/octal_nand/out_6: U3.6, U85.3 (~I6)
/octal_nand/out_7: U3.3, U85.4 (~I7)
/r1_out0: U11.2 (A0), U14.2 (Q0), U107.2 (A0)
/r1_out1: U11.3 (A1), U14.5 (Q1), U107.3 (A1)
/r1_out2: U11.4 (A2), U14.6 (Q2), U107.4 (A2)
/r1_out3: U11.5 (A3), U14.9 (Q3), U107.5 (A3)
/r1_out4: U11.6 (A4), U14.12 (Q4), U107.6 (A4)
/r1_out5: U11.7 (A5), U14.15 (Q5), U107.7 (A5)
/r1_out6: U11.8 (A6), U14.16 (Q6), U107.8 (A6)
/r1_out7: U11.9 (A7), U14.19 (Q7), U107.9 (A7)
/r1_out8: U2.13, U12.2 (A0), U20.2 (Q0), U108.2 (A0)
/r1_out9: U2.10, U12.3 (A1), U20.5 (Q1), U108.3 (A1)
/r1_out10: U2.5, U12.4 (A2), U20.6 (Q2), U108.4 (A2)
/r1_out11: U2.2, U12.5 (A3), U20.9 (Q3), U108.5 (A3)
/r1_out12: U3.13, U12.6 (A4), U20.12 (Q4), U108.6 (A4)
/r1_out13: U3.10, U12.7 (A5), U20.15 (Q5), U108.7 (A5)
/r1_out14: U3.5, U12.8 (A6), U20.16 (Q6), U108.8 (A6)
/r1_out15: U3.2, U12.9 (A7), U20.19 (Q7), U108.9 (A7)
/r1we: R1318.1, U4.12, U4.13, U7.19 (CE), U8.19 (CE), U17.13, U29.8 (I1)
/write_enable: Dd7.2 (A), J6.16, U17.3, U30.1 (COM)
GND: C1.2, C3.2, C4.2, C5.2, C6.2, C7.2, C8.2, C9.2, C10.2, C11.2, C12.2, C13.2, C14.2, C15.2, C16.2, C17.2, C18.2, C19.2, C20.2, C21.2, C22.2, C23.2, C24.2, C25.2, C26.2, C27.2, C28.2, C29.2, C30.2, C31.2, C32.2, C33.2, C34.2, C35.2, C36.2, C37.2, C38.2, C39.2, C40.2, C41.2, C42.2, C43.2, C44.2, C45.2, C46.2, C47.2, C48.2, C49.2, C50.2, C51.2, C52.2, C53.2, C54.2, C55.2, C56.2, C57.2, C58.2, C59.2, C60.2, C61.2, C62.2, C63.2, C64.2, C65.2, C66.2, C67.2, C68.2, C69.2, C70.2, C71.2, C72.2, C73.2, C74.2, C75.2, C76.2, C77.2, C78.2, C79.2, C80.2, C81.2, C82.2, C83.2, C84.2, C87.2, C88.2, H1.1 (1_1), H2.1 (1_1), H3.1 (1_1), H4.1 (1_1), J4.7, J4.8, J4.13, J4.14, J5.2, J5.8, J5.14, J5.20, J6.2, J6.8, J6.14, J6.20, R1.2, Rd1.2, Rd2.2, Rd3.2, Rd4.2, Rd5.2, Rd6.2, Rd7.2, U1.10 (GND), U2.7 (GND), U3.7 (GND), U4.7 (GND), U5.10 (GND), U6.10 (GND), U7.10 (GND), U8.10 (GND), U9.10 (GND), U10.10 (GND), U11.10 (GND), U12.10 (GND), U14.10 (GND), U15.10 (GND), U16.10 (GND), U17.7 (GND), U18.10 (GND), U19.10 (GND), U20.10 (GND), U21.2 (A0), U21.3 (A1), U21.4 (A2), U21.5 (A3), U21.6 (A4), U21.7 (A5), U21.8 (A6), U21.9 (A7), U21.10 (GND), U22.2 (A0), U22.3 (A1), U22.4 (A2), U22.5 (A3), U22.6 (A4), U22.7 (A5), U22.8 (A6), U22.9 (A7), U22.10 (GND), U23.10 (GND), U24.10 (GND), U25.10 (GND), U26.10 (GND), U27.10 (GND), U28.10 (GND), U29.12 (GND), U30.12 (GND), U31.10 (GND), U32.10 (GND), U33.10 (GND), U34.10 (GND), U35.10 (GND), U36.10 (GND), U37.10 (GND), U38.10 (GND), U39.10 (GND), U40.10 (GND), U41.10 (GND), U42.10 (GND), U43.10 (GND), U44.10 (GND), U45.10 (GND), U46.10 (GND), U47.10 (GND), U48.10 (GND), U49.10 (GND), U50.10 (GND), U51.1 (~E), U51.10 (GND), U52.10 (GND), U53.1 (~E), U53.10 (GND), U81.10 (GND), U82.10 (GND), U85.5 (~EI), U85.8 (GND), U91.7 (GND), U92.7 (GND), U107.10 (GND), U108.10 (GND), U109.10 (GND), U110.10 (GND), U111.10 (GND), U112.10 (GND), U113.10 (GND), U114.10 (GND), U115.10 (GND), U116.10 (GND), U117.10 (GND), U118.10 (GND), U119.10 (GND), U120.10 (GND), U121.10 (GND), U122.10 (GND), U123.10 (GND), U124.10 (GND), U125.10 (GND), U126.10 (GND), U127.10 (GND), U128.10 (GND), U129.10 (GND), U130.10 (GND), U131.10 (GND), U132.10 (GND), U133.10 (GND), U134.10 (GND), U135.10 (GND), U136.10 (GND)
unnamed: D1.1 (K), R1.1
unnamed: Dd1.1 (K), Rd1.1
unnamed: Dd2.1 (K), Rd2.1
unnamed: Dd3.1 (K), Rd3.1
unnamed: Dd4.1 (K), Rd4.1
unnamed: Dd5.1 (K), Rd5.1
unnamed: Dd6.1 (K), Rd6.1
unnamed: Dd7.1 (K), Rd7.1
unnamed: U4.3, U4.4, U4.5
unnamed: U4.6, U4.10
unnamed: U4.9, U4.11
unnamed: U17.4, U29.1 (COM)
unnamed: U91.3, U92.1
unnamed: U91.6, U92.2
unnamed: U91.8, U92.9
unnamed: U91.11, U92.10
unnamed: U92.3, U92.4
unnamed: U92.5, U92.8
